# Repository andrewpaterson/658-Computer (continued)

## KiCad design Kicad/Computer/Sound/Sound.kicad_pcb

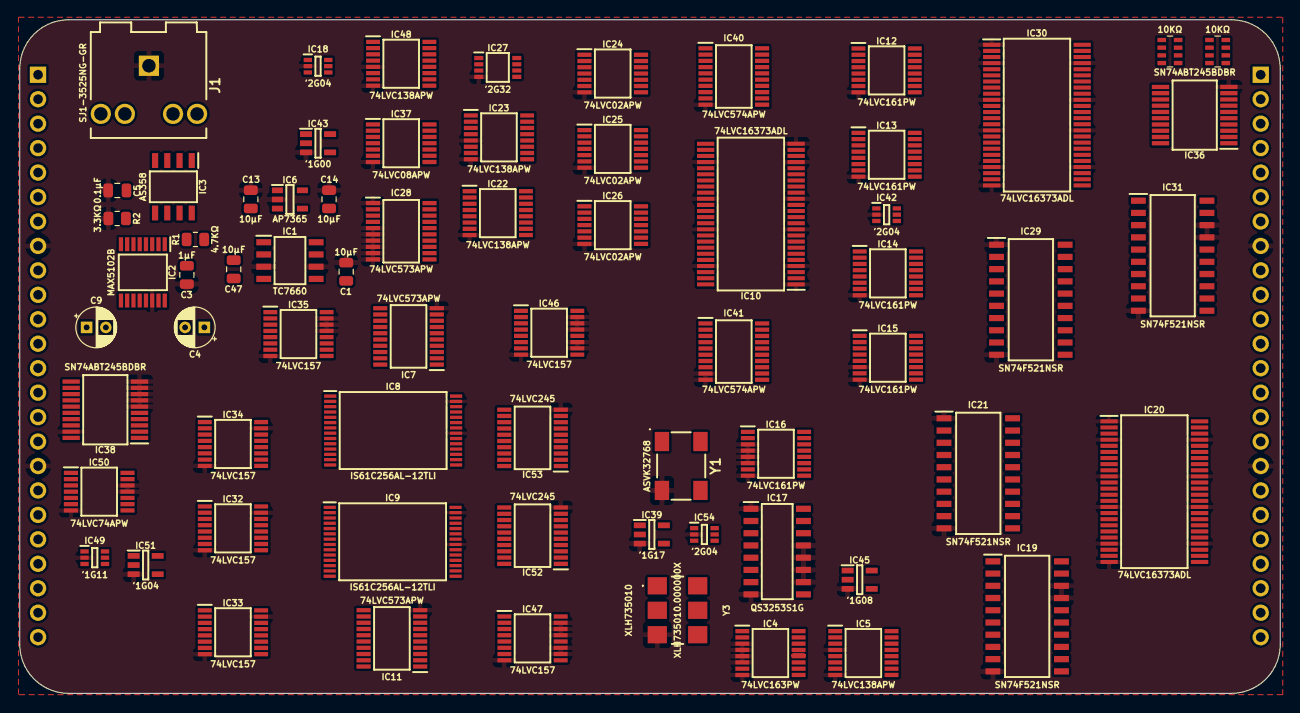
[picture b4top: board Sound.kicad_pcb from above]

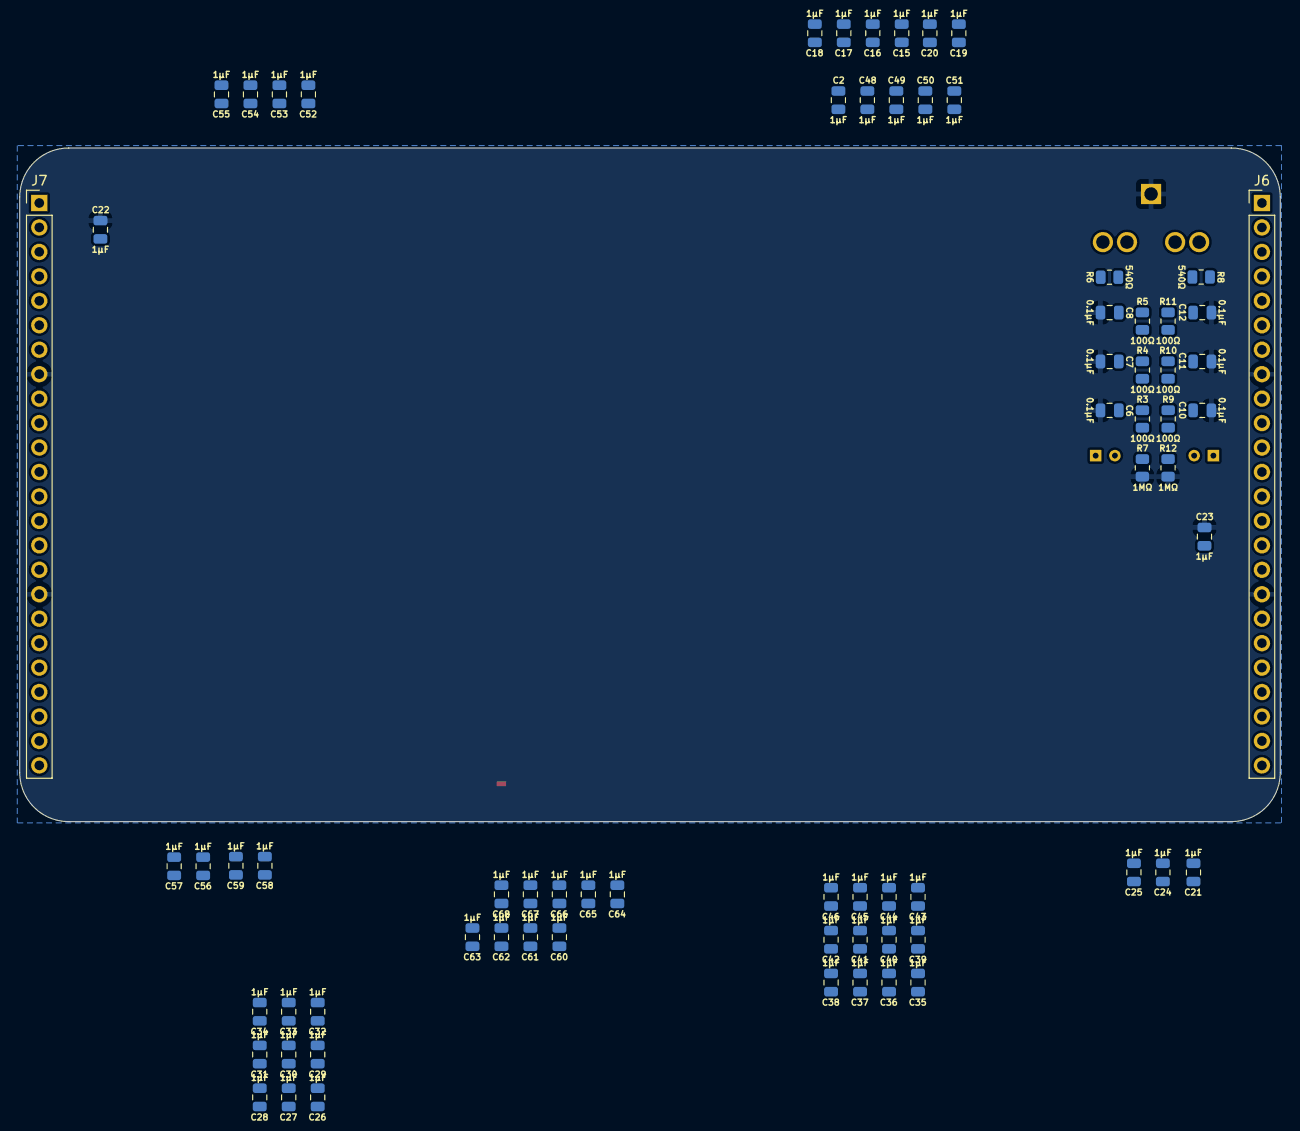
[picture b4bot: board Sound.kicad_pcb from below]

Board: 2 copper layers, 130.9 x 70.0 mm, 141 parts (72 on the bottom side), 233 nets, no tracks yet.

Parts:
C1, C13, C14, C47: 10µF; C_0805
C2, C3, C15, C16, C17, C18, C19, C20, C21, C22, C23, C24, C25, C26, C27, C28, C29, C30, C31, C32, C33, C34, C35, C36, C37, C38, C39, C40, C41, C42, C43, C44, C45, C46, C48, C49, C50, C51, C52, C53, C54, C55, C56, C57, C58, C59, C60, C61, C62, C63, C64, C65, C66, C67, C68: 1μF; C_0805
C4, C9: C_Polarized; CP_Radial_D4.0mm_P2.00mm
C5, C6, C7, C8, C10, C11, C12: 0.1μF; C_0805
IC1: TC7660EOA; SOIC127P600X175-8N
IC2: MAX5102BEUE+T; SOP65P640X110-16N
IC3: AS358AMTR-G1; SOIC127P600X175-8N
IC4: 74LVC163PW,118; SOP65P640X110-16N
IC5, IC22, IC23, IC48: 74LVC138APW-Q100J; SOP65P640X110-16N
IC6: AP7365-33WG-7; SOT95P285X130-5N
IC7, IC11, IC28: 74LVC573APW,118; SOP65P640X110-20N
IC8, IC9: IS61C256AL-12TLI; SOP55P1340X120-28N
IC10, IC20, IC30: 74LVC16373ADL,118; SOP64P1025X280-48N
IC12, IC13, IC14, IC15, IC16: 74LVC161PW,112; SOP65P640X110-16N
IC17: QS3253S1G; SOIC127P602X173-16N
IC18, IC42, IC54: 74LVC2G04GW-Q100H; SOP65P210X110-6N
IC19, IC21, IC29, IC31: SN74F521NSR; SOIC127P780X200-20N
IC24, IC25, IC26: 74LVC02APW,118; SOP65P640X110-14N
IC27: 74LVC2G32DP,125; SOP65P400X110-8N
IC32, IC33, IC34, IC35, IC46, IC47: 74LVC157APW,118; SOP65P640X110-16N
IC36, IC38: SN74ABT245BDBR; SOP65P780X200-20N
IC37: 74LVC08APW,112; SOP65P640X110-14N
IC39: 74LVC1G17GV,125; SOT95P275X110-5N
IC40, IC41: 74LVC574APW,118; SOP65P640X110-20N
IC43: 74LVC1G00GV,125; SOT95P275X110-5N
IC45: 74LVC1G08GV,125; SOT95P275X110-5N
IC49: 74LVC1G11GW-Q100H; SOP65P210X110-6N
IC50: 74LVC74APW,118; SOP65P640X110-14N
IC51: 74LVC1G04GV,125; SOT95P275X110-5N
IC52, IC53: 74LVC245AT20; SOP65P640X120-20N
J1: SJ1-3525NG-GR; SJ13525NGGR
J6, J7: Conn_01x24_Pin; PinHeader_1x24_P2.54mm_Vertical
NT1: NetTie; NetTie-2_SMD_Pad0.5mm
R1: 4.7KΩ; R_0805
R2: 3.3KΩ; R_0805
R3, R4, R5, R9, R10, R11: 100Ω; R_0805
R6, R8: 540Ω; R_0805
R7, R12: 1MΩ; R_0805
RN1, RN2: CAY16-103J4LF; CAY16-J4
Y1: ASVK-32.768KHZ-LJT; ASVK32768KHZLJT
Y3: XLH735010.000000X; XLH735010000000X

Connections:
/Sound Clock/3.3V: C2.1, C14.1, C15.1, C16.1, C17.1, C18.1, C19.1, C20.1, C21.1, C24.1, C25.1, C26.1, C27.1, C28.1, C29.1, C30.1, C31.1, C32.1, C33.1, C34.1, C35.1, C36.1, C37.1, C38.1, C39.1, C40.1, C41.1, C42.1, C43.1, C44.1, C48.1, C49.1, C50.1, C51.1, C52.1, C53.1, C56.1, C57.1, C61.1, C62.1, C63.1, C64.1, C65.1, C66.1, C67.1, C68.1, IC4.9 (~PE), IC4.10 (CET), IC4.16 (3V), IC5.16 (3V), IC6.5 (VOUT), IC7.20 (3V), IC10.7 (3V), IC10.18 (3V), IC10.31 (3V), IC10.42 (3V), IC11.20 (3V), IC12.7 (CEP), IC12.10 (CET), IC12.16 (3V), IC13.10 (CET), IC13.16 (3V), IC14.16 (3V), IC15.16 (3V), IC16.7 (CEP), IC16.9 (~PE), IC16.10 (CET), IC16.16 (3V), IC17.15 (~EB), IC18.5 (3V), IC20.7 (3V), IC20.18 (3V), IC20.31 (3V), IC20.42 (3V), IC22.6 (E3), IC22.16 (3V), IC23.16 (3V), IC24.14 (3V), IC25.14 (3V), IC26.9 (3A), IC26.12 (4A), IC26.14 (3V), IC27.8 (VCC), IC28.20 (3V), IC30.7 (3V), IC30.18 (3V), IC30.31 (3V), IC30.42 (3V), IC32.16 (3V), IC33.16 (3V), IC34.16 (3V), IC35.16 (3V), IC37.14 (3V), IC39.5 (3V), IC40.20 (3V), IC41.20 (3V), IC42.5 (3V), IC43.5 (3V), IC45.5 (3V), IC46.6 (2I1), IC46.16 (3V), IC47.6 (2I1), IC47.16 (3V), IC48.16 (3V), IC49.5 (3V), IC50.1 (~1RD), IC50.14 (3V), IC51.5 (3V), IC52.20 (3V), IC53.20 (3V), IC54.5 (3V), RN1.5 (R4), RN1.6 (R3), RN1.7 (R2), RN1.8 (R1), RN2.5 (R4), RN2.6 (R3), RN2.7 (R2), RN2.8 (R1), Y1.4 (3V), Y3.6 (3V)
/Sound Clock/4KHz: IC16.12 (Q2), IC17.3 (I3A)
/Sound Clock/5V: C3.1, C13.1, C22.1, C23.1, C45.1, C46.1, C54.1, C55.1, C58.1, C59.1, C60.1, IC1.8 (V+), IC2.1 (VDD), IC3.8 (VCC), IC6.1 (VIN), IC6.3 (EN), IC8.7 (5V), IC9.7 (5V), IC17.16 (5V), IC19.20 (5V), IC21.20 (5V), IC29.20 (5V), IC31.20 (5V), IC36.20 (5V), IC38.1 (DIR), IC38.20 (5V), J6.3, J7.22, R1.1
/Sound Clock/8KHz: IC16.13 (Q1), IC17.4 (I2A)
/Sound Clock/10MHz: IC4.2 (CP), Y3.4 (OUT)
/Sound Clock/16KHz: IC16.14 (Q0), IC17.5 (I1A)
/Sound Clock/32KHz: IC16.2 (CP), IC17.6 (I0A), Y1.3 (OUTPUT)
/Sound Clock/-5V: C1.2, IC1.5 (VOUT), IC3.4 (GND)
/Sound Clock/A0: IC22.1 (A0), IC23.1 (A0), IC33.2 (1I0), J7.10
/Sound Clock/A1: IC22.2 (A1), IC23.2 (A1), IC33.5 (2I0), J7.11
/Sound Clock/A2: IC22.3 (A2), IC23.3 (A2), IC33.11 (3I0), J7.12
/Sound Clock/A3: IC22.5 (~E2), IC23.6 (E3), IC33.14 (4I0), J7.13
/Sound Clock/A4: IC32.2 (1I0), J7.14
/Sound Clock/A5: IC32.5 (2I0), J7.15
/Sound Clock/A6: IC32.11 (3I0), J7.16
/Sound Clock/A7: IC32.14 (4I0), J7.18
/Sound Clock/A8: IC34.2 (1I0), J7.19
/Sound Clock/A9: IC34.5 (2I0), J7.20
/Sound Clock/A10: IC34.11 (3I0), J7.21
/Sound Clock/A11: IC34.14 (4I0), J7.23
/Sound Clock/A12: IC35.2 (1I0), J7.24
/Sound Clock/A13: IC35.5 (2I0), J6.24
/Sound Clock/A14: IC35.11 (3I0), J6.23
/Sound Clock/A15: IC48.1 (A0), J6.22
/Sound Clock/A16: IC27.6 (2B), IC37.1 (1A), IC43.2 (A), IC48.6 (E3), J6.21
/Sound Clock/A ~OE: IC8.1 (~OE), IC46.4 (1Y)
/Sound Clock/A ~WE: IC8.6 (~WE), IC46.7 (2Y)
/Sound Clock/B ~OE: IC9.1 (~OE), IC47.4 (1Y)
/Sound Clock/B ~WE: IC9.6 (~WE), IC47.7 (2Y)
/Sound Clock/C0: IC12.14 (Q0), IC21.3 (Q0), IC29.3 (Q0), IC33.3 (1I1), IC40.2 (D0)
/Sound Clock/C1: IC12.13 (Q1), IC21.5 (Q1), IC29.5 (Q1), IC33.6 (2I1), IC40.3 (D1)
/Sound Clock/C2: IC12.12 (Q2), IC21.7 (Q2), IC29.7 (Q2), IC33.10 (3I1), IC40.4 (D2)
/Sound Clock/C3: IC12.11 (Q3), IC21.9 (Q3), IC29.9 (Q3), IC33.13 (4I1), IC40.5 (D3)
/Sound Clock/C4: IC13.14 (Q0), IC21.12 (Q4), IC29.12 (Q4), IC32.3 (1I1), IC40.6 (D4)
/Sound Clock/C5: IC13.13 (Q1), IC21.14 (Q5), IC29.14 (Q5), IC32.6 (2I1), IC40.7 (D5)
/Sound Clock/C6: IC13.12 (Q2), IC21.16 (Q6), IC29.16 (Q6), IC32.10 (3I1), IC40.8 (D6)
/Sound Clock/C7: IC13.11 (Q3), IC21.18 (Q7), IC29.18 (Q7), IC32.13 (4I1), IC40.9 (D7)
/Sound Clock/C8: IC14.14 (Q0), IC19.3 (Q0), IC31.3 (Q0), IC34.3 (1I1), IC41.2 (D0)
/Sound Clock/C9: IC14.13 (Q1), IC19.5 (Q1), IC31.5 (Q1), IC34.6 (2I1), IC41.3 (D1)
/Sound Clock/C10: IC14.12 (Q2), IC19.7 (Q2), IC31.7 (Q2), IC34.10 (3I1), IC41.4 (D2)
/Sound Clock/C11: IC14.11 (Q3), IC19.9 (Q3), IC31.9 (Q3), IC34.13 (4I1), IC41.5 (D3)
/Sound Clock/C12: IC15.14 (Q0), IC19.12 (Q4), IC31.12 (Q4), IC35.3 (1I1), IC41.6 (D4)
/Sound Clock/C13: IC15.13 (Q1), IC19.14 (Q5), IC31.14 (Q5), IC35.6 (2I1), IC41.7 (D5)
/Sound Clock/C14: IC15.12 (Q2), IC19.16 (Q6), IC31.16 (Q6), IC35.10 (3I1), IC41.8 (D6)
/Sound Clock/CLK: IC12.2 (CP), IC13.2 (CP), IC14.2 (CP), IC15.2 (CP), IC27.1 (1A), IC39.4 (Y), IC46.3 (1I1), IC47.3 (1I1), IC54.3 (2A)
/Sound Clock/CPU A ~OE: IC37.4 (2A), IC46.2 (1I0), IC48.13 (~Y2)
/Sound Clock/CPU A ~OE·~WE: IC37.6 (2Y), IC53.19 (~OE)
/Sound Clock/CPU A ~WE: IC37.5 (2B), IC46.5 (2I0), IC48.11 (~Y4)
/Sound Clock/CPU B ~OE: IC37.9 (3A), IC47.2 (1I0), IC48.12 (~Y3)
/Sound Clock/CPU B ~OE·~WE: IC37.8 (3Y), IC52.19 (~OE)
/Sound Clock/CPU B ~WE: IC37.10 (3B), IC47.5 (2I0), IC48.10 (~Y5)
/Sound Clock/Clear Interrupt: IC25.8 (3Y), IC51.2 (A)
/Sound Clock/Clear Interrupt ~CS: IC22.9 (~Y6), IC25.9 (3A)
/Sound Clock/Clock Select _{S0}: IC17.14 (S0), IC28.19 (Q0)
/Sound Clock/Clock Select _{S1}: IC17.2 (S1), IC28.18 (Q1)
/Sound Clock/Config ~CS: IC22.4 (~E1), IC23.4 (~E1), IC27.3 (2Y)
/Sound Clock/D0: IC10.26 (2D7), IC10.37 (1D7), IC20.36 (2D0), IC20.47 (1D0), IC28.2 (D0), IC30.36 (2D0), IC30.47 (1D0), IC36.11 (B7), IC40.19 (Q0), IC41.19 (Q0), IC52.2 (A0), IC53.2 (A0), RN2.1 (R1)
/Sound Clock/D0_{IN/OUT}: IC36.9 (A7), J7.1
/Sound Clock/D1: IC10.27 (2D6), IC10.38 (1D6), IC20.35 (2D1), IC20.46 (1D1), IC28.3 (D1), IC30.35 (2D1), IC30.46 (1D1), IC36.12 (B6), IC40.18 (Q1), IC41.18 (Q1), IC52.3 (A1), IC53.3 (A1), RN2.2 (R2)
/Sound Clock/D1_{IN/OUT}: IC36.8 (A6), J7.2
/Sound Clock/D2: IC10.29 (2D5), IC10.40 (1D5), IC20.33 (2D2), IC20.44 (1D2), IC28.4 (D2), IC30.33 (2D2), IC30.44 (1D2), IC36.13 (B5), IC40.17 (Q2), IC41.17 (Q2), IC52.4 (A2), IC53.4 (A2), RN2.3 (R3)
/Sound Clock/D2_{IN/OUT}: IC36.7 (A5), J7.3
/Sound Clock/D3: IC10.30 (2D4), IC10.41 (1D4), IC20.32 (2D3), IC20.43 (1D3), IC30.32 (2D3), IC30.43 (1D3), IC36.14 (B4), IC40.16 (Q3), IC41.16 (Q3), IC52.5 (A3), IC53.5 (A3), RN2.4 (R4)
/Sound Clock/D3_{IN/OUT}: IC36.6 (A4), J7.4
/Sound Clock/D4: IC10.32 (2D3), IC10.43 (1D3), IC20.30 (2D4), IC20.41 (1D4), IC30.30 (2D4), IC30.41 (1D4), IC36.15 (B3), IC40.15 (Q4), IC41.15 (Q4), IC52.6 (A4), IC53.6 (A4), RN1.4 (R4)
/Sound Clock/D4_{IN/OUT}: IC36.5 (A3), J7.5
/Sound Clock/D5: IC10.33 (2D2), IC10.44 (1D2), IC20.29 (2D5), IC20.40 (1D5), IC30.29 (2D5), IC30.40 (1D5), IC36.16 (B2), IC40.14 (Q5), IC41.14 (Q5), IC52.7 (A5), IC53.7 (A5), RN1.3 (R3)
/Sound Clock/D5_{IN/OUT}: IC36.4 (A2), J7.6
/Sound Clock/D6: IC10.35 (2D1), IC10.46 (1D1), IC20.27 (2D6), IC20.38 (1D6), IC30.27 (2D6), IC30.38 (1D6), IC36.17 (B1), IC40.13 (Q6), IC41.13 (Q6), IC52.8 (A6), IC53.8 (A6), RN1.2 (R2)
/Sound Clock/D6_{IN/OUT}: IC36.3 (A1), J7.7
/Sound Clock/D7: IC10.36 (2D0), IC10.47 (1D0), IC20.26 (2D7), IC20.37 (1D7), IC30.26 (2D7), IC30.37 (1D7), IC36.18 (B0), IC40.12 (Q7), IC41.12 (Q7), IC52.9 (A7), IC53.9 (A7), RN1.1 (R1)
/Sound Clock/D7_{IN/OUT}: IC36.2 (A0), J7.9
/Sound Clock/DA0: IC7.2 (D0), IC8.18 (I/O0), IC53.18 (B0)
/Sound Clock/DA1: IC7.3 (D1), IC8.19 (I/O1), IC53.17 (B1)
/Sound Clock/DA2: IC7.4 (D2), IC8.20 (I/O2), IC53.16 (B2)
/Sound Clock/DA3: IC7.5 (D3), IC8.22 (I/O3), IC53.15 (B3)
/Sound Clock/DA4: IC7.6 (D4), IC8.23 (I/O4), IC53.14 (B4)
/Sound Clock/DA5: IC7.7 (D5), IC8.24 (I/O5), IC53.13 (B5)
/Sound Clock/DA6: IC7.8 (D6), IC8.25 (I/O6), IC53.12 (B6)
/Sound Clock/DA7: IC7.9 (D7), IC8.26 (I/O7), IC53.11 (B7)
/Sound Clock/DB0: IC9.18 (I/O0), IC11.2 (D0), IC52.18 (B0)
/Sound Clock/DB1: IC9.19 (I/O1), IC11.3 (D1), IC52.17 (B1)
/Sound Clock/DB2: IC9.20 (I/O2), IC11.4 (D2), IC52.16 (B2)
/Sound Clock/DB3: IC9.22 (I/O3), IC11.5 (D3), IC52.15 (B3)
/Sound Clock/DB4: IC9.23 (I/O4), IC11.6 (D4), IC52.14 (B4)
/Sound Clock/DB5: IC9.24 (I/O5), IC11.7 (D5), IC52.13 (B5)
/Sound Clock/DB6: IC9.25 (I/O6), IC11.8 (D6), IC52.12 (B6)
/Sound Clock/DB7: IC9.26 (I/O7), IC11.9 (D7), IC52.11 (B7)
/Sound Clock/Device CS: IC18.6 (1Y), IC37.2 (1B), IC43.1 (B)
/Sound Clock/Device ~CS: IC18.1 (1A), IC27.5 (2A), IC36.19 (~OE), IC38.15 (B3), IC48.4 (~E1)
/Sound Clock/Device ~CS _{IN}: IC38.5 (A3), J6.11
/Sound Clock/EC0: IC20.2 (1Q0), IC21.2 (P0)
/Sound Clock/EC1: IC20.3 (1Q1), IC21.4 (P1)
/Sound Clock/EC2: IC20.5 (1Q2), IC21.6 (P2)
/Sound Clock/EC3: IC20.6 (1Q3), IC21.8 (P3)
/Sound Clock/EC4: IC20.8 (1Q4), IC21.11 (P4)
/Sound Clock/EC5: IC20.9 (1Q5), IC21.13 (P5)
/Sound Clock/EC6: IC20.11 (1Q6), IC21.15 (P6)
/Sound Clock/EC7: IC20.12 (1Q7), IC21.17 (P7)
/Sound Clock/EC8: IC19.2 (P0), IC20.13 (2Q0)
/Sound Clock/EC9: IC19.4 (P1), IC20.14 (2Q1)
/Sound Clock/EC10: IC19.6 (P2), IC20.16 (2Q2)
/Sound Clock/EC11: IC19.8 (P3), IC20.17 (2Q3)
/Sound Clock/EC12: IC19.11 (P4), IC20.19 (2Q4)
/Sound Clock/EC13: IC19.13 (P5), IC20.20 (2Q5)
/Sound Clock/EC14: IC19.15 (P6), IC20.22 (2Q6)
/Sound Clock/Enable: IC12.1 (~MR), IC13.1 (~MR), IC14.1 (~MR), IC15.1 (~MR), IC37.12 (4A), IC50.9 (2Q)
/Sound Clock/GND: C1.1, C2.2, C3.2, C5.1, C6.1, C7.1, C8.1, C10.1, C11.1, C12.1, C13.2, C14.2, C15.2, C16.2, C17.2, C18.2, C19.2, C20.2, C21.2, C22.2, C23.2, C24.2, C25.2, C26.2, C27.2, C28.2, C29.2, C30.2, C31.2, C32.2, C33.2, C34.2, C35.2, C36.2, C37.2, C38.2, C39.2, C40.2, C41.2, C42.2, C43.2, C44.2, C45.2, C46.2, C48.2, C49.2, C50.2, C51.2, C52.2, C53.2, C54.2, C55.2, C56.2, C57.2, C58.2, C59.2, C60.2, C61.2, C62.2, C63.2, C64.2, C65.2, C66.2, C67.2, C68.2, IC1.3 (GND), IC1.6 (LV), IC2.14 (GND), IC4.3 (D0), IC4.4 (D1), IC4.5 (D2), IC4.6 (D3), IC4.8 (GND), IC5.4 (~E1), IC5.8 (GND), IC6.2 (GND), IC7.10 (GND), IC8.21 (GND), IC8.27 (~CE), IC9.21 (GND), IC9.27 (~CE), IC10.1 (1~OE), IC10.4 (GND), IC10.10 (GND), IC10.15 (GND), IC10.21 (GND), IC10.24 (2~OE), IC10.28 (GND), IC10.34 (GND), IC10.39 (GND), IC10.45 (GND), IC11.10 (GND), IC12.8 (GND), IC13.8 (GND), IC14.8 (GND), IC15.6 (D3), IC15.8 (GND), IC16.3 (D0), IC16.4 (D1), IC16.5 (D2), IC16.6 (D3), IC16.8 (GND), IC17.1 (~EA), IC17.8 (GND), IC17.10 (I0B), IC17.11 (I1B), IC17.12 (I2B), IC17.13 (I3B), IC18.2 (GND), IC19.10 (GND), IC19.17 (P7), IC19.18 (Q7), IC20.1 (1~OE), IC20.4 (GND), IC20.10 (GND), IC20.15 (GND), IC20.21 (GND), IC20.24 (2~OE), IC20.28 (GND), IC20.34 (GND), IC20.39 (GND), IC20.45 (GND), IC21.1 (~OE), IC21.10 (GND), IC22.8 (GND), IC23.5 (~E2), IC23.8 (GND), IC24.7 (GND), IC25.7 (GND), IC26.7 (GND), IC27.4 (GND), IC28.1 (~OE), IC28.5 (D3), IC28.6 (D4), IC28.7 (D5), IC28.8 (D6), IC28.9 (D7), IC28.10 (GND), IC29.1 (~OE), IC29.10 (GND), IC30.1 (1~OE), IC30.4 (GND), IC30.10 (GND), IC30.15 (GND), IC30.21 (GND), IC30.24 (2~OE), IC30.28 (GND), IC30.34 (GND), IC30.39 (GND), IC30.45 (GND), IC31.10 (GND), IC31.17 (P7), IC31.18 (Q7), IC32.8 (GND), IC32.15 (~E), IC33.8 (GND), IC33.15 (~E), IC34.8 (GND), IC34.15 (~E), IC35.8 (GND), IC35.13 (4I1), IC35.14 (4I0), IC35.15 (~E), IC36.10 (GND), IC37.7 (GND), IC38.6 (A4), IC38.7 (A5), IC38.8 (A6), IC38.9 (A7), IC38.10 (GND), IC38.19 (~OE), IC39.3 (GND), IC40.10 (GND), IC41.9 (D7), IC41.10 (GND), IC42.2 (GND), IC43.3 (GND), IC45.3 (GND), IC46.8 (GND), IC46.10 (3I1), IC46.11 (3I0), IC46.13 (4I1), IC46.14 (4I0), IC46.15 (~E), IC47.8 (GND), IC47.10 (3I1), IC47.11 (3I0), IC47.13 (4I1), IC47.14 (4I0), IC47.15 (~E), IC48.5 (~E2), IC48.8 (GND), IC49.2 (GND), IC50.7 (GND), IC50.11 (2CP), IC50.12 (2D), IC51.3 (GND), IC52.10 (GND), IC53.10 (GND), IC54.2 (GND), J1.1 (GND), J6.8, J6.17, J7.8, J7.17, R2.1, R7.1, R12.1, Y1.2 (GND), Y3.3 (GND)
/Sound Clock/IC0: IC29.2 (P0), IC30.2 (1Q0)
/Sound Clock/IC1: IC29.4 (P1), IC30.3 (1Q1)
/Sound Clock/IC2: IC29.6 (P2), IC30.5 (1Q2)
/Sound Clock/IC3: IC29.8 (P3), IC30.6 (1Q3)
/Sound Clock/IC4: IC29.11 (P4), IC30.8 (1Q4)
/Sound Clock/IC5: IC29.13 (P5), IC30.9 (1Q5)
/Sound Clock/IC6: IC29.15 (P6), IC30.11 (1Q6)
/Sound Clock/IC7: IC29.17 (P7), IC30.12 (1Q7)
/Sound Clock/IC8: IC30.13 (2Q0), IC31.2 (P0)
/Sound Clock/IC9: IC30.14 (2Q1), IC31.4 (P1)
/Sound Clock/IC10: IC30.16 (2Q2), IC31.6 (P2)
/Sound Clock/IC11: IC30.17 (2Q3), IC31.8 (P3)
/Sound Clock/IC12: IC30.19 (2Q4), IC31.11 (P4)
/Sound Clock/IC13: IC30.20 (2Q5), IC31.13 (P5)
/Sound Clock/IC14: IC30.22 (2Q6), IC31.15 (P6)
/Sound Clock/Interrupt Enable: IC37.11 (4Y), IC49.3 (B)
/Sound Clock/LC0: IC10.23 (2Q7), IC12.3 (D0)
/Sound Clock/LC1: IC10.22 (2Q6), IC12.4 (D1)
/Sound Clock/LC2: IC10.20 (2Q5), IC12.5 (D2)
/Sound Clock/LC3: IC10.19 (2Q4), IC12.6 (D3)
/Sound Clock/LC4: IC10.17 (2Q3), IC13.3 (D0)
/Sound Clock/LC5: IC10.16 (2Q2), IC13.4 (D1)
/Sound Clock/LC6: IC10.14 (2Q1), IC13.5 (D2)
/Sound Clock/LC7: IC10.13 (2Q0), IC13.6 (D3)
/Sound Clock/LC8: IC10.12 (1Q7), IC14.3 (D0)
/Sound Clock/LC9: IC10.11 (1Q6), IC14.4 (D1)
/Sound Clock/LC10: IC10.9 (1Q5), IC14.5 (D2)
/Sound Clock/LC11: IC10.8 (1Q4), IC14.6 (D3)
/Sound Clock/LC12: IC10.6 (1Q3), IC15.3 (D0)
/Sound Clock/LC13: IC10.5 (1Q2), IC15.4 (D1)
/Sound Clock/LC14: IC10.3 (1Q1), IC15.5 (D2)
/Sound Clock/Line Out Left: J1.3 (L), R6.2
/Sound Clock/Line Out Right: J1.2 (R), R8.2
/Sound Clock/M0: IC8.17 (A0), IC9.17 (A0), IC33.4 (1Y)
/Sound Clock/M1: IC8.16 (A1), IC9.16 (A1), IC33.7 (2Y)
/Sound Clock/M2: IC8.15 (A2), IC9.15 (A2), IC33.9 (3Y)
/Sound Clock/M3: IC8.14 (A3), IC9.14 (A3), IC33.12 (4Y)
/Sound Clock/M4: IC8.13 (A4), IC9.13 (A4), IC32.4 (1Y)
/Sound Clock/M5: IC8.12 (A5), IC9.12 (A5), IC32.7 (2Y)
/Sound Clock/M6: IC8.11 (A6), IC9.11 (A6), IC32.9 (3Y)
/Sound Clock/M7: IC8.10 (A7), IC9.10 (A7), IC32.12 (4Y)
/Sound Clock/M8: IC8.4 (A8), IC9.4 (A8), IC34.4 (1Y)
/Sound Clock/M9: IC8.3 (A9), IC9.3 (A9), IC34.7 (2Y)
/Sound Clock/M10: IC8.28 (A10), IC9.28 (A10), IC34.9 (3Y)
/Sound Clock/M11: IC8.2 (A11), IC9.2 (A11), IC34.12 (4Y)
/Sound Clock/M12: IC8.9 (A12), IC9.9 (A12), IC35.4 (1Y)
/Sound Clock/M13: IC8.5 (A13), IC9.5 (A13), IC35.7 (2Y)
/Sound Clock/M14: IC8.8 (A14), IC9.8 (A14), IC35.9 (3Y)
/Sound Clock/MAX0: IC2.9 (D3), IC7.19 (Q0), IC11.19 (Q0)
/Sound Clock/MAX1: IC2.10 (D2), IC7.18 (Q1), IC11.18 (Q1)
/Sound Clock/MAX2: IC2.11 (D1), IC7.17 (Q2), IC11.17 (Q2)
/Sound Clock/MAX3: IC2.12 (D0), IC7.16 (Q3), IC11.16 (Q3)
/Sound Clock/MAX4: IC2.8 (D4), IC7.15 (Q4), IC11.15 (Q4)
/Sound Clock/MAX5: IC2.7 (D5), IC7.14 (Q5), IC11.14 (Q5)
/Sound Clock/MAX6: IC2.6 (D6), IC7.13 (Q6), IC11.13 (Q6)
/Sound Clock/MAX7: IC2.5 (D7), IC7.12 (Q7), IC11.12 (Q7)
/Sound Clock/MAX_{A0}: IC2.13 (A0), NT1.2
/Sound Clock/MAX_{~WR}: IC2.4 (~WR), IC45.4 (Y)
/Sound Clock/Q0: IC4.14 (Q0), IC5.1 (A0)
/Sound Clock/Q1: IC4.13 (Q1), IC5.2 (A1)
/Sound Clock/Q2: IC4.12 (Q2), IC5.3 (A2), NT1.1
/Sound Clock/Q3: IC4.11 (Q3), IC5.5 (~E2), IC54.1 (1A)
/Sound Clock/Read Address High: IC26.6 (2Y), IC42.3 (2A)
/Sound Clock/Read Address High ~CS: IC23.14 (~Y1), IC26.5 (2B)
/Sound Clock/Read Address Low: IC26.3 (1Y), IC40.11 (CP), IC41.11 (CP), IC42.1 (1A)
/Sound Clock/Read Address Low ~CS: IC23.15 (~Y0), IC26.2 (1B)
/Sound Clock/Reset Disable ~CS: IC23.7 (~Y7), IC50.10 (~2SD)
/Sound Clock/Sound Address: IC7.11 (LE), IC11.11 (LE), IC18.4 (2Y)
/Sound Clock/TC_{0..3}: IC12.15 (TC), IC13.7 (CEP), IC14.7 (CEP), IC15.7 (CEP)
/Sound Clock/TC_{4..7}: IC13.15 (TC), IC14.10 (CET)
/Sound Clock/TC_{8..11}: IC14.15 (TC), IC15.10 (CET)
/Sound Clock/Write End Address High: IC20.25 (2LE), IC24.11 (4Y)
/Sound Clock/Write End Address High ~CS: IC22.12 (~Y3), IC24.12 (4A)
/Sound Clock/Write End Address Low: IC20.48 (1LE), IC24.8 (3Y)
/Sound Clock/Write End Address Low ~CS: IC22.13 (~Y2), IC24.9 (3A)
/Sound Clock/Write Flags: IC25.11 (4Y), IC28.11 (LE)
/Sound Clock/Write Flags ~CS: IC22.7 (~Y7), IC25.12 (4A)
/Sound Clock/Write Interrupt Address High: IC25.6 (2Y), IC30.25 (2LE)
/Sound Clock/Write Interrupt Address High ~CS: IC22.10 (~Y5), IC25.4 (2A)
/Sound Clock/Write Interrupt Address Low: IC25.3 (1Y), IC30.48 (1LE)
/Sound Clock/Write Interrupt Address Low ~CS: IC22.11 (~Y4), IC25.1 (1A)
/Sound Clock/Write Start Address High: IC10.25 (2LE), IC24.6 (2Y)
/Sound Clock/Write Start Address High ~CS: IC22.14 (~Y1), IC24.4 (2A)
/Sound Clock/Write Start Address Low: IC10.48 (1LE), IC24.3 (1Y)
/Sound Clock/Write Start Address Low ~CS: IC22.15 (~Y0), IC24.1 (1A)
/Sound Clock/~CLK: IC4.1 (~MR), IC5.6 (E3), IC50.3 (1CP), IC54.4 (2Y)
/Sound Clock/~CPU Address: IC32.1 (S), IC33.1 (S), IC34.1 (S), IC35.1 (S), IC43.4 (Y), IC46.1 (S), IC47.1 (S)
/Sound Clock/~Clear Interrupt: IC49.6 (C), IC51.4 (Y)
/Sound Clock/~Enable _{OUT}: IC2.3 (SHDN), IC50.8 (~2Q), J6.19
/Sound Clock/~End _{CMP}: IC12.9 (~PE), IC13.9 (~PE), IC14.9 (~PE), IC15.9 (~PE), IC19.19 (~P=Q)
/Sound Clock/~Interrupt _{CMP}: IC31.19 (~P=Q), IC50.2 (1D)
/Sound Clock/~Interrupt _{OUT}: IC50.5 (1Q), J6.18
/Sound Clock/~Q3: IC4.7 (CEP), IC54.6 (1Y)
/Sound Clock/~RD: IC26.1 (1A), IC26.4 (2A), IC36.1 (DIR), IC38.16 (B2), IC48.3 (A2), IC52.1 (DIR), IC53.1 (DIR)
/Sound Clock/~RD_{IN}: IC38.4 (A2), J6.13
/Sound Clock/~Read Address High: IC41.1 (~OE), IC42.4 (2Y)
/Sound Clock/~Read Address Low: IC40.1 (~OE), IC42.6 (1Y), J6.10
/Sound Clock/~Reset: IC16.1 (~MR), IC38.18 (B0), IC49.1 (A), IC50.13 (~2RD)
/Sound Clock/~Reset _{IN}: IC38.2 (A0), J6.1
/Sound Clock/~Sound Address: IC18.3 (2A), IC27.7 (1Y)
/Sound Clock/~WD: IC24.2 (1B), IC24.5 (2B), IC24.10 (3B), IC24.13 (4B), IC25.2 (1B), IC25.5 (2B), IC25.10 (3B), IC25.13 (4B), IC26.10 (3B), IC26.13 (4B), IC38.17 (B1), IC48.2 (A1)
/Sound Clock/~WD_{IN}: IC38.3 (A1), J6.12
/Sound Clock/~WR_{A}: IC5.14 (~Y1), IC7.1 (~OE), IC45.2 (A)
/Sound Clock/~WR_{B}: IC5.12 (~Y3), IC11.1 (~OE), IC45.1 (B)
unnamed: C4.2, R3.1, R7.2
unnamed: C6.2, R3.2, R4.1
unnamed: C7.2, R4.2, R5.1
unnamed: C9.2, R9.1, R12.2
unnamed: C10.2, R9.2, R10.1
unnamed: C11.2, R10.2, R11.1
unnamed: C47.1, IC1.2 (CAP+)
unnamed: C47.2, IC1.4 (CAP-)
unnamed: C4.1, IC2.16 (OUTA)
unnamed: C9.1, IC2.15 (OUTB)
unnamed: C5.2, IC2.2 (REF), R1.2, R2.2
unnamed: C8.2, IC3.3 (IN_1+), R5.2
unnamed: IC3.1 (OUT_1), IC3.2 (IN_1-), R6.1
unnamed: C12.2, IC3.5 (IN_2+), R11.2
unnamed: IC3.6 (IN_2-), IC3.7 (OUT_2), R8.1
unnamed: IC17.7 (YA), IC39.2 (A)
unnamed: IC19.1 (~OE), IC21.19 (~P=Q)
unnamed: IC27.2 (1B), IC37.3 (1Y)
unnamed: IC28.17 (Q2), IC37.13 (4B)
unnamed: IC29.19 (~P=Q), IC31.1 (~OE)
unnamed: IC49.4 (Y), IC50.4 (~1SD)

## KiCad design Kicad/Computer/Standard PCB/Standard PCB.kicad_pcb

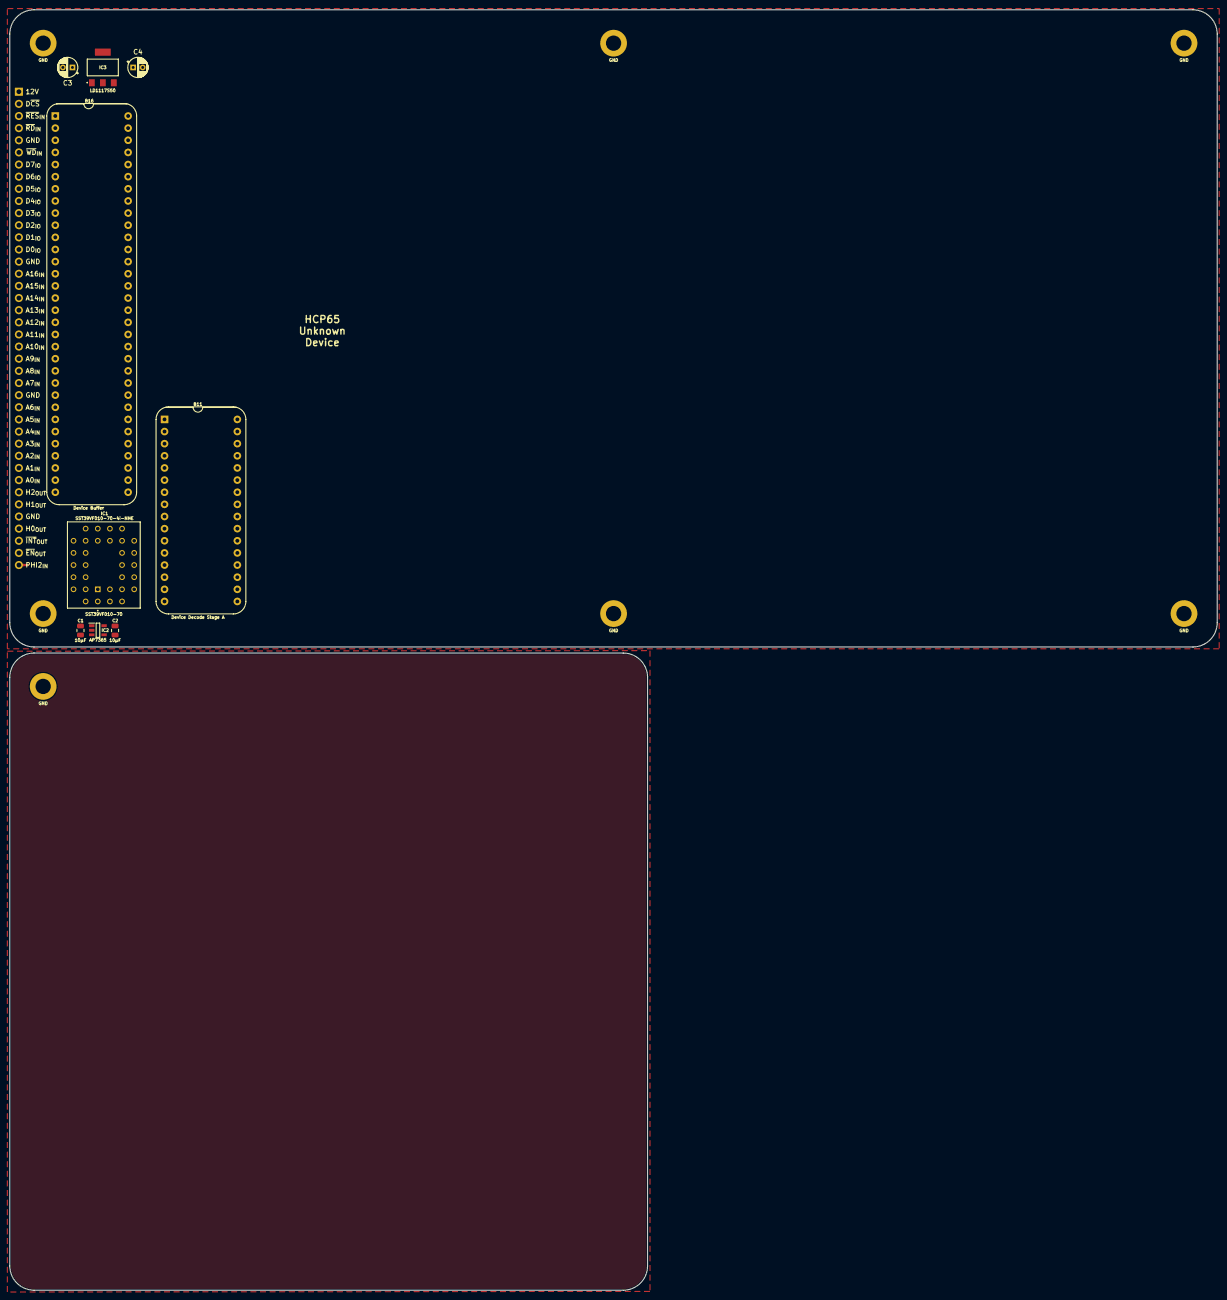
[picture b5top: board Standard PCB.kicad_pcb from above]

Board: 2 copper layers, 252.7 x 268.0 mm, 18 parts (1 on the bottom side), 63 nets, no tracks yet.

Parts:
B11: Device Decode Stage A; HCP65_Device_Decode_Stage_A
B16: Device Buffer; HCP65_Device_Buffer
C1, C2: 10µF; C_0805
C3, C4: C_Polarized; CP_Radial_D4.0mm_P2.00mm
H1, H1#2, H2, H3, H4, H5, H6: MountingHole_Pad; HCP65_MountingHole_M3_
IC1: SST39VF010-70-4I-NHE; 5408803224008
IC2: AP7365-33WG-7; SOT95P285X130-5N
IC3: LD1117S50C; LD1117S33C
J1: Conn_01x40_Pin; PinHeader_1x40_P2.54mm_Vertical
NT1: NetTie_2; NetTie-2_SMD_Pad0.5mm

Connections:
/3.3V: C2.1, IC1.32 (3V), IC2.5 (VOUT)
/5V: B11.1 (5V), B11.17 (5V), B16.3 (5V), B16.35 (5V), C1.1, C3.1, IC2.1 (VIN), IC2.3 (EN), IC3.2 (5.0VOut)
/12V: C4.1, IC3.3 (15VIn), J1.1
/A0: B16.33 (A0), IC1.12 (A0)
/A0_{IN}: B16.32 (A0_{IN}), J1.33
/A1: B16.34 (A1), IC1.11 (A1)
/A1_{IN}: B16.31 (A1_{IN}), J1.32
/A2: B16.36 (A2), IC1.10 (A2)
/A2_{IN}: B16.30 (A2_{IN}), J1.31
/A3: B11.13 (A3), B16.37 (A3), IC1.9 (A3)
/A3_{IN}: B16.29 (A3_{IN}), J1.30
/A4: B11.11 (A4), B16.38 (A4), IC1.8 (A4)
/A4_{IN}: B16.28 (A4_{IN}), J1.29
/A5: B16.39 (A5), IC1.7 (A5)
/A5_{IN}: B16.27 (A5_{IN}), J1.28
/A6: B16.40 (A6), IC1.6 (A6)
/A6_{IN}: B16.26 (A6_{IN}), J1.27
/A7: B16.41 (A7), IC1.5 (A7)
/A7_{IN}: B16.25 (A7_{IN}), J1.25
/A8: B16.43 (A8), IC1.27 (A8)
/A8_{IN}: B16.24 (A8_{IN}), J1.24
/A9: B16.44 (A9), IC1.26 (A9)
/A9_{IN}: B16.22 (A9_{IN}), J1.23
/A10: B11.10 (A10), B16.45 (A10), IC1.23 (A10)
/A10_{IN}: B16.21 (A10_{IN}), J1.22
/A11: B11.9 (A11), B16.46 (A11), IC1.25 (A11)
/A11_{IN}: B16.20 (A11_{IN}), J1.21
/A12: B11.8 (A12), B16.47 (A12), IC1.4 (A12)
/A12_{IN}: B16.19 (A12_{IN}), J1.20
/A13: B11.7 (A13), B16.48 (A13), IC1.28 (A13)
/A13_{IN}: B16.18 (A13_{IN}), J1.19
/A14: B11.6 (A14), B16.49 (A14), IC1.29 (A14)
/A14_{IN}: B16.17 (A14_{IN}), J1.18
/A15: B11.4 (A15), B16.50 (A15)
/A15_{IN}: B16.16 (A15_{IN}), J1.17
/A16: B11.3 (A16), B16.51 (A16)
/A16_{IN}: B16.15 (A16_{IN}), J1.16
/D0: B16.56 (D0), IC1.13 (DQ0)
/D0_{IN/OUT}: B16.11 (D0_{IN/OUT}), J1.14
/D1: B16.57 (D1), IC1.14 (DQ1)
/D1_{IN/OUT}: B16.9 (D1_{IN/OUT}), J1.13
/D2: B16.58 (D2), IC1.15 (DQ2)
/D2_{IN/OUT}: B16.8 (D2_{IN/OUT}), J1.12
/D3: B16.59 (D3), IC1.17 (DQ3)
/D3_{IN/OUT}: B16.7 (D3_{IN/OUT}), J1.11
/D4: B16.60 (D4), IC1.18 (DQ4)
/D4_{IN/OUT}: B16.6 (D4_{IN/OUT}), J1.10
/D5: B16.61 (D5), IC1.19 (DQ5)
/D5_{IN/OUT}: B16.5 (D5_{IN/OUT}), J1.9
/D6: B16.62 (D6), IC1.20 (DQ6)
/D6_{IN/OUT}: B16.4 (D6_{IN/OUT}), J1.8
/D7: B16.63 (D7), IC1.21 (DQ7)
/D7_{IN/OUT}: B16.2 (D7_{IN/OUT}), J1.7
/Device ~CS: B11.2 (~Device_Select), B16.64 (~Device_Select)
/Device ~CS _{IN}: B16.1 (~Device_Select_{IN}), J1.2
/GND: B11.5 (GND), B11.12 (GND), B11.21 (GND), B11.28 (GND), B16.10 (GND), B16.14 (S_{IN}), B16.23 (GND), B16.42 (GND), B16.55 (GND), C1.2, C2.2, C3.2, C4.2, H1.1 (GND), H1#2.1 (GND), H2.1 (GND), H3.1 (GND), H4.1 (GND), H5.1 (GND), H6.1 (GND), IC1.2 (A16), IC1.3 (A15), IC1.16 (GND), IC2.2 (GND), IC3.1 (GND), J1.5, J1.15, J1.26, J1.36
/PHI2_{IN}: J1.40, NT1.1
/~Device ROM: B11.25 (~Device_ROM), IC1.22 (~CE)
/~RD: B16.54 (~RD_{OUT}), IC1.24 (~OE)
/~RD_{IN}: B16.12 (~RD_{IN}), J1.4
/~Reset _{IN}: B11.15 (~Reset_{IN}), J1.3
/~WD: B16.53 (~WD_{OUT}), IC1.31 (~WE)
/~WD_{IN}: B16.13 (~WD_{IN}), J1.6

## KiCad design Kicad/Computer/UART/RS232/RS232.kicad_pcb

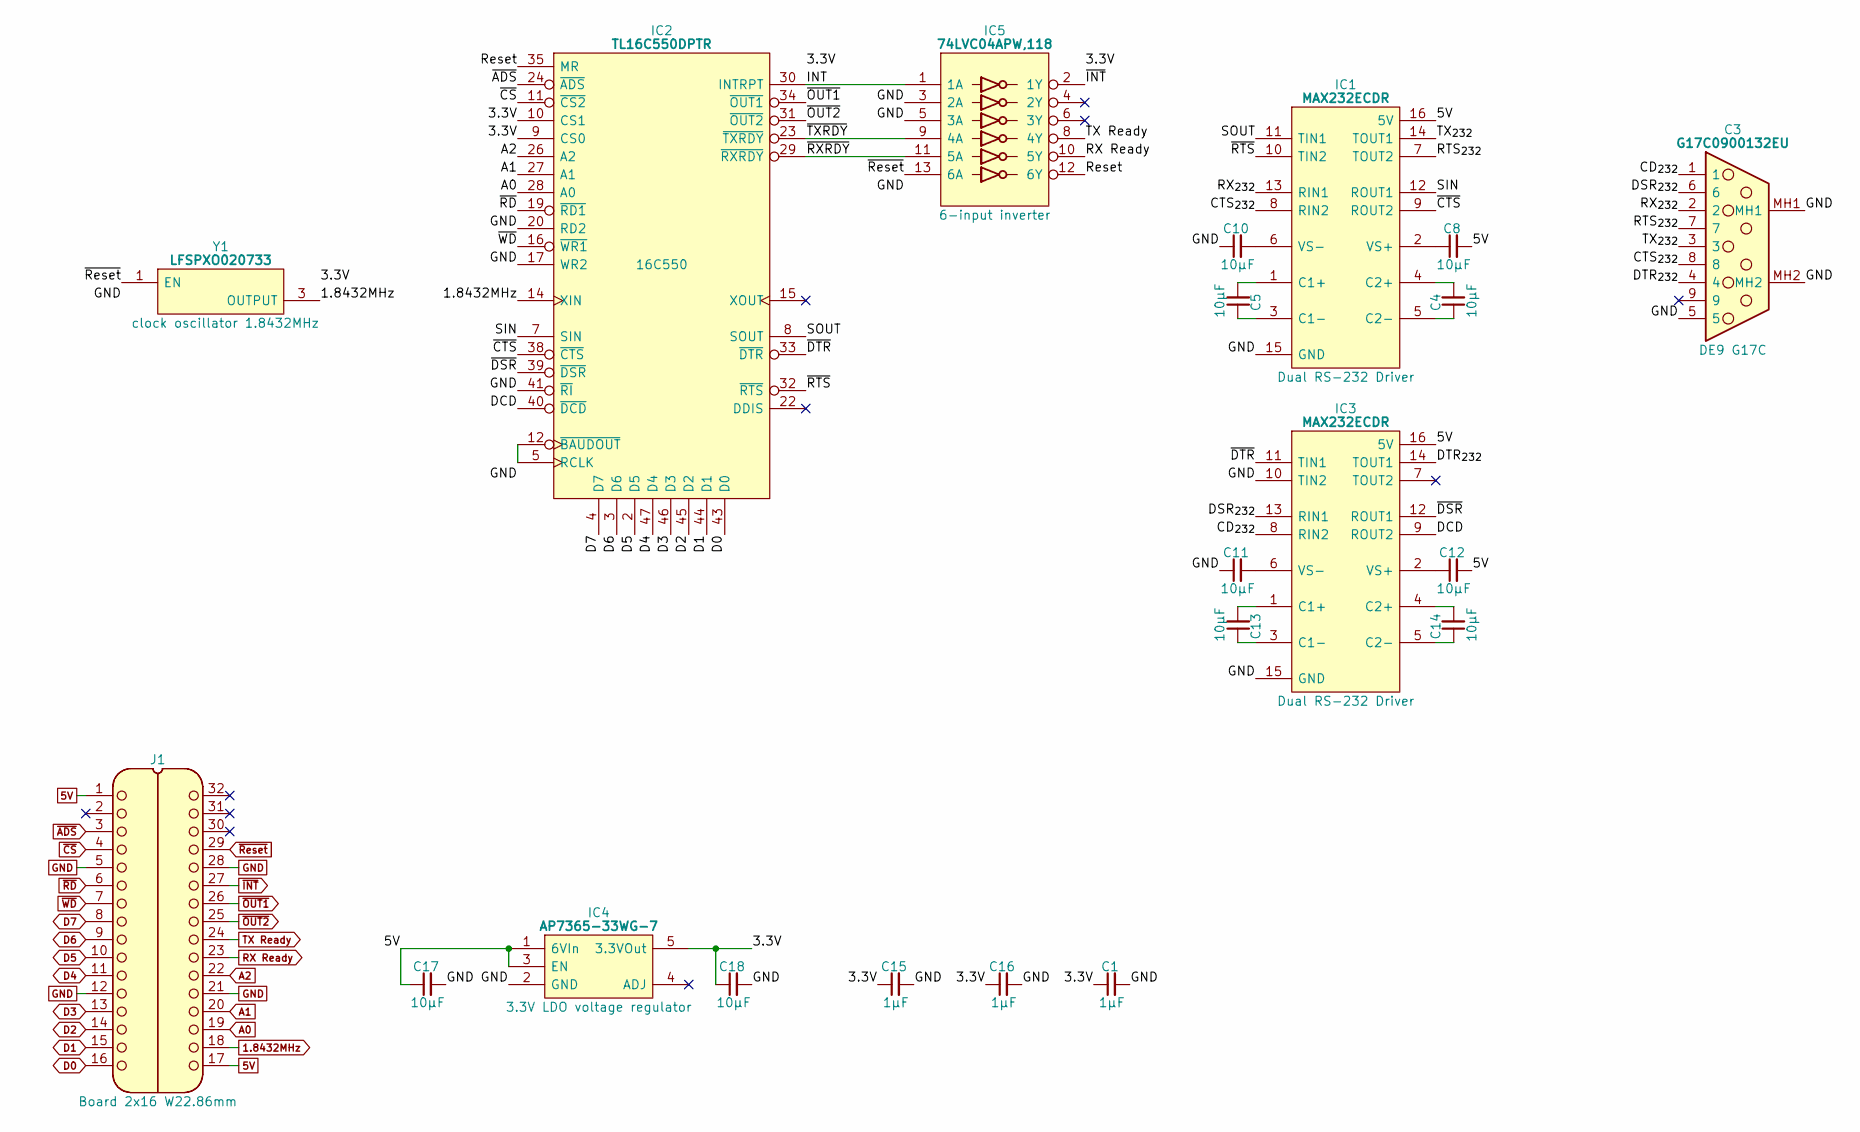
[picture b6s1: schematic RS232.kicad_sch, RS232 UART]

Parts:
C1, C15, C16: 1μF; C_0805
C3: G17C0900132EU; Manufacturer_Part_Number G17C0900132EU; Mouser Part Number 523-G17C0900132EU
C4, C5, C8, C10, C11, C12, C13, C14: 10μF; C_0805
C17, C18: 10µF; C_0805
IC1, IC3: MAX232ECDR; SOIC127P600X175-16N; Manufacturer_Part_Number MAX232ECDR; Mouser Part Number 595-MAX232ECDR
IC2: TL16C550DPTR; QFP50P900X900X160-48N; Manufacturer_Part_Number TL16C550DPTR; Mouser Part Number 595-TL16C550DPTR
IC4: AP7365-33WG-7; SOT95P285X130-5N; Manufacturer_Part_Number AP7365-33WG-7; Mouser Part Number 621-AP7365-33WG-7
IC5: 74LVC04APW,118; SOP65P640X110-14N; Manufacturer_Part_Number 74LVC04APW,118; Mouser Part Number 771-74LVC04APW-T
J1: Board 2x16 W22.86mm; DIP-32_Board_W22.86mm_Nak
Y1: LFSPXO020733

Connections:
1.8432MHz: IC2.14 (XIN), J1.18, Y1.3 (OUTPUT)
5V: C8.2, C12.2, C17.1, IC1.16 (5V), IC3.16 (5V), IC4.1 (6VIn), IC4.3 (EN), J1.1, J1.17
/3.3V: C1.1, C15.1, C16.1, C18.1, IC2.9 (CS0), IC2.10 (CS1), IC2.42 (5V), IC4.5 (3.3VOut), IC5.14 (3V), Y1.4 (3V)
/CD_{232}: C3.1, IC3.8 (RIN2)
/CTS_{232}: C3.8, IC1.8 (RIN2)
/DCD: IC2.40 (~DCD), IC3.9 (ROUT2)
/DSR_{232}: C3.6, IC3.13 (RIN1)
/DTR_{232}: C3.4, IC3.14 (TOUT1)
/INT: IC2.30 (INTRPT), IC5.1 (1A)
/RTS_{232}: C3.7, IC1.7 (TOUT2)
/RX_{232}: C3.2, IC1.13 (RIN1)
/Reset: IC2.35 (MR), IC5.12 (6Y)
/SIN: IC1.12 (ROUT1), IC2.7 (SIN)
/SOUT: IC1.11 (TIN1), IC2.8 (SOUT)
/TX_{232}: C3.3, IC1.14 (TOUT1)
/~CTS: IC1.9 (ROUT2), IC2.38 (~CTS)
/~DSR: IC2.39 (~DSR), IC3.12 (ROUT1)
/~DTR: IC2.33 (~DTR), IC3.11 (TIN1)
/~RTS: IC1.10 (TIN2), IC2.32 (~RTS)
/~RXRDY: IC2.29 (~RXRDY), IC5.11 (5A)
/~TXRDY: IC2.23 (~TXRDY), IC5.9 (4A)
A0: IC2.28 (A0), J1.19
A1: IC2.27 (A1), J1.20
A2: IC2.26 (A2), J1.22
D0: IC2.43 (D0), J1.16
D1: IC2.44 (D1), J1.15
D2: IC2.45 (D2), J1.14
D3: IC2.46 (D3), J1.13
D4: IC2.47 (D4), J1.11
D5: IC2.2 (D5), J1.10
D6: IC2.3 (D6), J1.9
D7: IC2.4 (D7), J1.8
GND: C1.2, C3.5, C3.MH1, C3.MH2, C10.1, C11.1, C15.2, C16.2, C17.2, C18.2, IC1.15 (GND), IC2.17 (WR2), IC2.18 (GND), IC2.20 (RD2), IC2.41 (~RI), IC3.10 (TIN2), IC3.15 (GND), IC4.2 (GND), IC5.3 (2A), IC5.5 (3A), IC5.7 (GND), J1.5, J1.12, J1.21, J1.28, Y1.2 (GND)
unnamed: C5.2, IC1.1 (C1+)
unnamed: C5.1, IC1.3 (C1-)
unnamed: C4.2, IC1.4 (C2+)
unnamed: C4.1, IC1.5 (C2-)
unnamed: C8.1, IC1.2 (VS+)
unnamed: C10.2, IC1.6 (VS-)
unnamed: IC2.5 (RCLK), IC2.12 (~BAUDOUT)
unnamed: C13.2, IC3.1 (C1+)
unnamed: C13.1, IC3.3 (C1-)
unnamed: C14.2, IC3.4 (C2+)
unnamed: C14.1, IC3.5 (C2-)
unnamed: C12.1, IC3.2 (VS+)
unnamed: C11.2, IC3.6 (VS-)
RX Ready: IC5.10 (5Y), J1.23
TX Ready: IC5.8 (4Y), J1.24
~ADS: IC2.24 (~ADS), J1.3
~CS: IC2.11 (~CS2), J1.4
~INT: IC5.2 (1Y), J1.27
~OUT1: IC2.34 (~OUT1), J1.26
~OUT2: IC2.31 (~OUT2), J1.25
~RD: IC2.19 (~RD1), J1.6
~Reset: IC5.13 (6A), J1.29, Y1.1 (EN)
~WD: IC2.16 (~WR1), J1.7

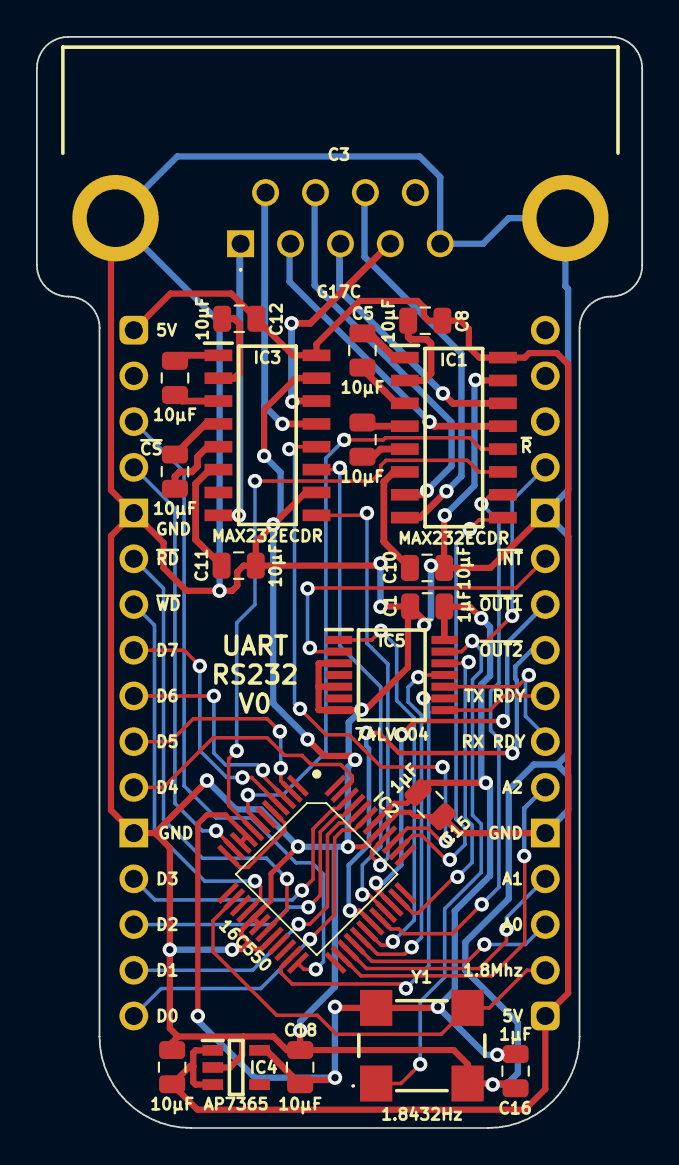
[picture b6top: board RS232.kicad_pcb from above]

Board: 2 copper layers, 33.6 x 60.6 mm, 21 parts (0 on the bottom side), 56 nets.
